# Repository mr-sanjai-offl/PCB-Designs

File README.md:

# PCB Designs

A collection of completed KiCad PCB design projects with automatically generated documentation and PCB renders.

## Projects

| Project Title | Description |
|---|---|
| [Queaky Stem Toy](./Queaky_STEM_Toy/README.md) | KiCad PCB design project. |

---

_Automatically updated: 2026-08-27 16:57 UTC_
_Total projects: 1_

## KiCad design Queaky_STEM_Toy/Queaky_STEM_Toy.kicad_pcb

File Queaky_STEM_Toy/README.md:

# Queaky Stem Toy

## Description
<!-- PROJECT_DESCRIPTION -->
KiCad PCB design project for Queaky Stem Toy.
<!-- /PROJECT_DESCRIPTION -->

## Board Specifications

| Specification | Details |
|---|---|
| Dimensions | 30.0 × 30.0 mm |
| Area | 900.0 mm² |
| Thickness | 1.6 mm |
| Copper Layers | 2 |

## Components (8)

| Reference | Value | Footprint | Description |
|---|---|---|---|
| C1 | 1nF | Capacitor_THT:C_Disc_D9.0mm_W5.0mm_P10.00mm | Unpolarized capacitor |
| C2 | 100uF | Capacitor_THT:CP_Radial_D8.0mm_P3.50mm | Polarized capacitor |
| R1 | 1K | Resistor_THT:R_Axial_DIN0309_L9.0mm_D3.2mm_P12.70mm_Horizontal | Resistor |
| R2 | 10K | Resistor_THT:R_Axial_DIN0309_L9.0mm_D3.2mm_P12.70mm_Horizontal | Resistor |
| TP1 | Battery | Connector_PinSocket_2.54mm:PinSocket_1x02_P2.54mm_Vertical | 2-polar test point |
| TP2 | Human_IP | Connector_PinSocket_2.54mm:PinSocket_1x02_P2.54mm_Vertical | 2-polar test point |
| TP3 | Buzzer | Connector_PinSocket_2.54mm:PinSocket_1x02_P2.54mm_Vertical | 2-polar test point |
| U1 | NE555P | Package_DIP:DIP-8_W7.62mm | Precision Timers, 555 compatible, PDIP-8 |

## PCB Renders

### Bottom View

### Rotating 3D View

### Top View

## KiCad Files

- `Queaky_STEM_Toy.kicad_pcb`
- `Queaky_STEM_Toy.kicad_prl`
- `Queaky_STEM_Toy.kicad_pro`
- `Queaky_STEM_Toy.kicad_sch`

---

_This README is automatically generated by GitHub Actions._

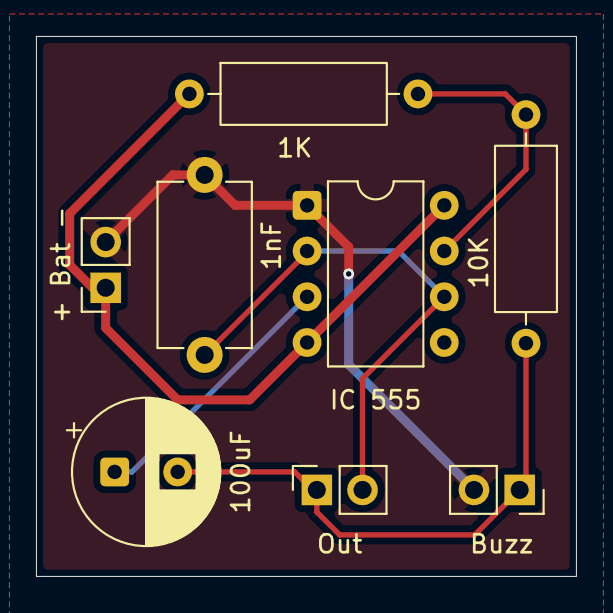
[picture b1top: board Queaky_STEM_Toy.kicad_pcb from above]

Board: 2 copper layers, 30.0 x 30.0 mm, 8 parts (0 on the bottom side), 6 nets.

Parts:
1K: 1K; R_Axial_DIN0309_L9.0mm_D3.2mm_P12.70mm_Horizontal
1nF: 1nF; C_Disc_D9.0mm_W5.0mm_P10.00mm
10K: 10K; R_Axial_DIN0309_L9.0mm_D3.2mm_P12.70mm_Horizontal
100uF: 100uF; CP_Radial_D8.0mm_P3.50mm
+ Bat -: Battery; PinSocket_1x02_P2.54mm_Vertical
Buzz: Buzzer; PinSocket_1x02_P2.54mm_Vertical
IC 555: NE555P; DIP-8_W7.62mm
Out: Human_IP; PinSocket_1x02_P2.54mm_Vertical

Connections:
/<NO NET>: 10K.2, 100uF.2, Buzz.1, Out.1
/DIS: 1K.2, 10K.1, IC 555.7 (DISCH)
/Out: 100uF.1, IC 555.3 (OUT)
/TR: 1nF.1, IC 555.2 (TRIG), IC 555.6 (THRES), Out.2
GND: 1nF.2, + Bat -.2, Buzz.2, IC 555.1 (GND)
VCC: 1K.1, + Bat -.1, IC 555.4 (~RST), IC 555.8 (VCC)

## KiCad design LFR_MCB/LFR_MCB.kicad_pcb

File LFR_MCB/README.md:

# Lfr Mcb

## Description
<!-- PROJECT_DESCRIPTION -->
KiCad PCB design project for Lfr Mcb.
<!-- /PROJECT_DESCRIPTION -->

## Board Specifications

| Specification | Details |
|---|---|
| Dimensions | 81.0 × 81.5 mm |
| Area | 6601.5 mm² |
| Thickness | 1.6 mm |
| Copper Layers | 2 |

## Components (17)

| Reference | Value | Footprint | Description |
|---|---|---|---|
| C1 | C | Capacitor_THT:C_Disc_D3.0mm_W1.6mm_P2.50mm | Unpolarized capacitor |
| C2 | C | Capacitor_THT:CP_Radial_D5.0mm_P2.50mm | Unpolarized capacitor |
| D1 | LED | LED_THT:LED_D5.0mm | Light emitting diode |
| D2 | D | Diode_THT:D_DO-41_SOD81_P10.16mm_Horizontal | Diode |
| J1 | Screw_Terminal_01x02 | TerminalBlock_Phoenix:TerminalBlock_Phoenix_MKDS-1,5-2-5.08_1x02_P5.08mm_Horizontal | Generic screw terminal, single row, 01x02, script generated (kicad-library-utils/schlib/autogen/connector/) |
| J10 | Conn_01x08_Socket | Connector_PinSocket_2.54mm:PinSocket_1x08_P2.54mm_Vertical | Generic connector, single row, 01x08, script generated |
| J2 | Screw_Terminal_01x02 | TerminalBlock_Phoenix:TerminalBlock_Phoenix_MKDS-1,5-2-5.08_1x02_P5.08mm_Horizontal | Generic screw terminal, single row, 01x02, script generated (kicad-library-utils/schlib/autogen/connector/) |
| J3 | Screw_Terminal_01x02 | TerminalBlock_Phoenix:TerminalBlock_Phoenix_MKDS-1,5-2-5.08_1x02_P5.08mm_Horizontal | Generic screw terminal, single row, 01x02, script generated (kicad-library-utils/schlib/autogen/connector/) |
| J4 | Conn_01x15_Socket | Connector_PinSocket_2.54mm:PinSocket_1x15_P2.54mm_Vertical | Generic connector, single row, 01x15, script generated |
| J5 | Conn_01x15_Socket | Connector_PinSocket_2.54mm:PinSocket_1x15_P2.54mm_Vertical | Generic connector, single row, 01x15, script generated |
| J6 | Conn_01x15_Socket | Connector_PinSocket_2.54mm:PinSocket_1x15_P2.54mm_Vertical | Generic connector, single row, 01x15, script generated |
| J9 | Conn_01x08_Socket | Connector_PinSocket_2.54mm:PinSocket_1x08_P2.54mm_Vertical | Generic connector, single row, 01x08, script generated |
| R1 | 360 | Resistor_THT:R_Axial_DIN0204_L3.6mm_D1.6mm_P5.08mm_Horizontal | Resistor |
| SW1 | SW_Wuerth_450301014042 | Button_Switch_THT:SW_Slide-03_Wuerth-WS-SLTV_10x2.5x6.4_P2.54mm | Switch slide, single pole double throw |
| SW2 | SW_Push | Button_Switch_THT:SW_CW_GPTS203211B | Push button switch, generic, two pins |
| SW3 | SW_Push | Button_Switch_THT:SW_CW_GPTS203211B | Push button switch, generic, two pins |
| U1 | LM2931AZ-5.0_TO92 | Package_TO_SOT_THT:TO-92_Inline | 100mA Low drop-out regulator, Fixed Output 5V, TO-92 |

## PCB Renders

### Bottom View

### Rotating 3D View

### Top View

## KiCad Files

- `LFR_MCB.kicad_pcb`
- `LFR_MCB.kicad_prl`
- `LFR_MCB.kicad_pro`
- `LFR_MCB.kicad_sch`

---

_This README is automatically generated by GitHub Actions._

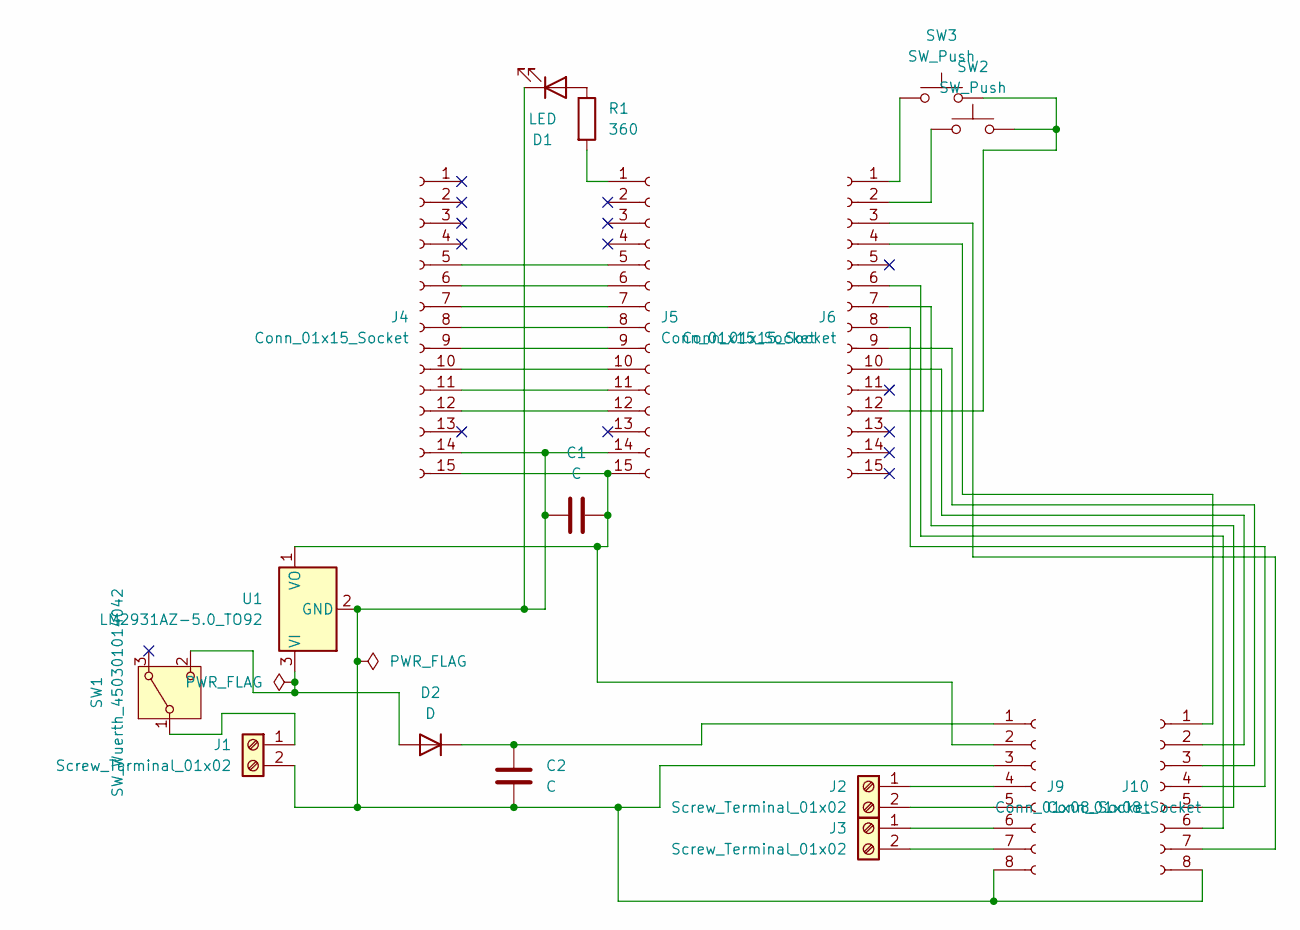
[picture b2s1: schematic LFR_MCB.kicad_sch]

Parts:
C1: C; C_Disc_D3.0mm_W1.6mm_P2.50mm
C2: C; CP_Radial_D5.0mm_P2.50mm
D1: LED; LED_D5.0mm
D2: D; D_DO-41_SOD81_P10.16mm_Horizontal
J1, J2, J3: Screw_Terminal_01x02; TerminalBlock_Phoenix_MKDS-1,5-2-5.08_1x02_P5.08mm_Horizont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
J4, J5, J6: Conn_01x15_Socket; PinSocket_1x15_P2.54mm_Vertical
J9, J10: Conn_01x08_Socket; PinSocket_1x08_P2.54mm_Vertical
R1: 360; R_Axial_DIN0204_L3.6mm_D1.6mm_P5.08mm_Horizontal
SW1: SW_Wuerth_450301014042; SW_Slide-03_Wuerth-WS-SLTV_10x2.5x6.4_P2.54mm
SW2, SW3: SW_Push; SW_CW_GPTS203211B
U1: LM2931AZ-5.0_TO92; TO-92_Inline

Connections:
unnamed: D1.2 (A), R1.1
unnamed: C1.1, C2.2, D1.1 (K), J1.2, J4.14, J5.14, J9.3, J9.8, J10.8, U1.2 (GND)
unnamed: D2.2 (A), SW1.2 (C), U1.3 (VI)
unnamed: C2.1, D2.1 (K), J9.1
unnamed: J1.1, SW1.1 (B)
unnamed: J2.1, J9.4
unnamed: J2.2, J9.5
unnamed: J3.1, J9.6
unnamed: J3.2, J9.7
unnamed: J4.5, J5.5
unnamed: J4.6, J5.6
unnamed: J4.7, J5.7
unnamed: J4.8, J5.8
unnamed: J4.9, J5.9
unnamed: J4.10, J5.10
unnamed: J4.11, J5.11
unnamed: J4.12, J5.12
unnamed: C1.2, J4.15, J5.15, J9.2, U1.1 (VO)
unnamed: J5.1, R1.2
unnamed: J6.1, SW3.1
unnamed: J6.2, SW2.1
unnamed: J6.12, SW2.2, SW3.2
unnamed: J6.4, J10.1
unnamed: J6.10, J10.2
unnamed: J6.9, J10.3
unnamed: J6.8, J10.4
unnamed: J6.7, J10.5
unnamed: J6.6, J10.6
unnamed: J6.3, J10.7

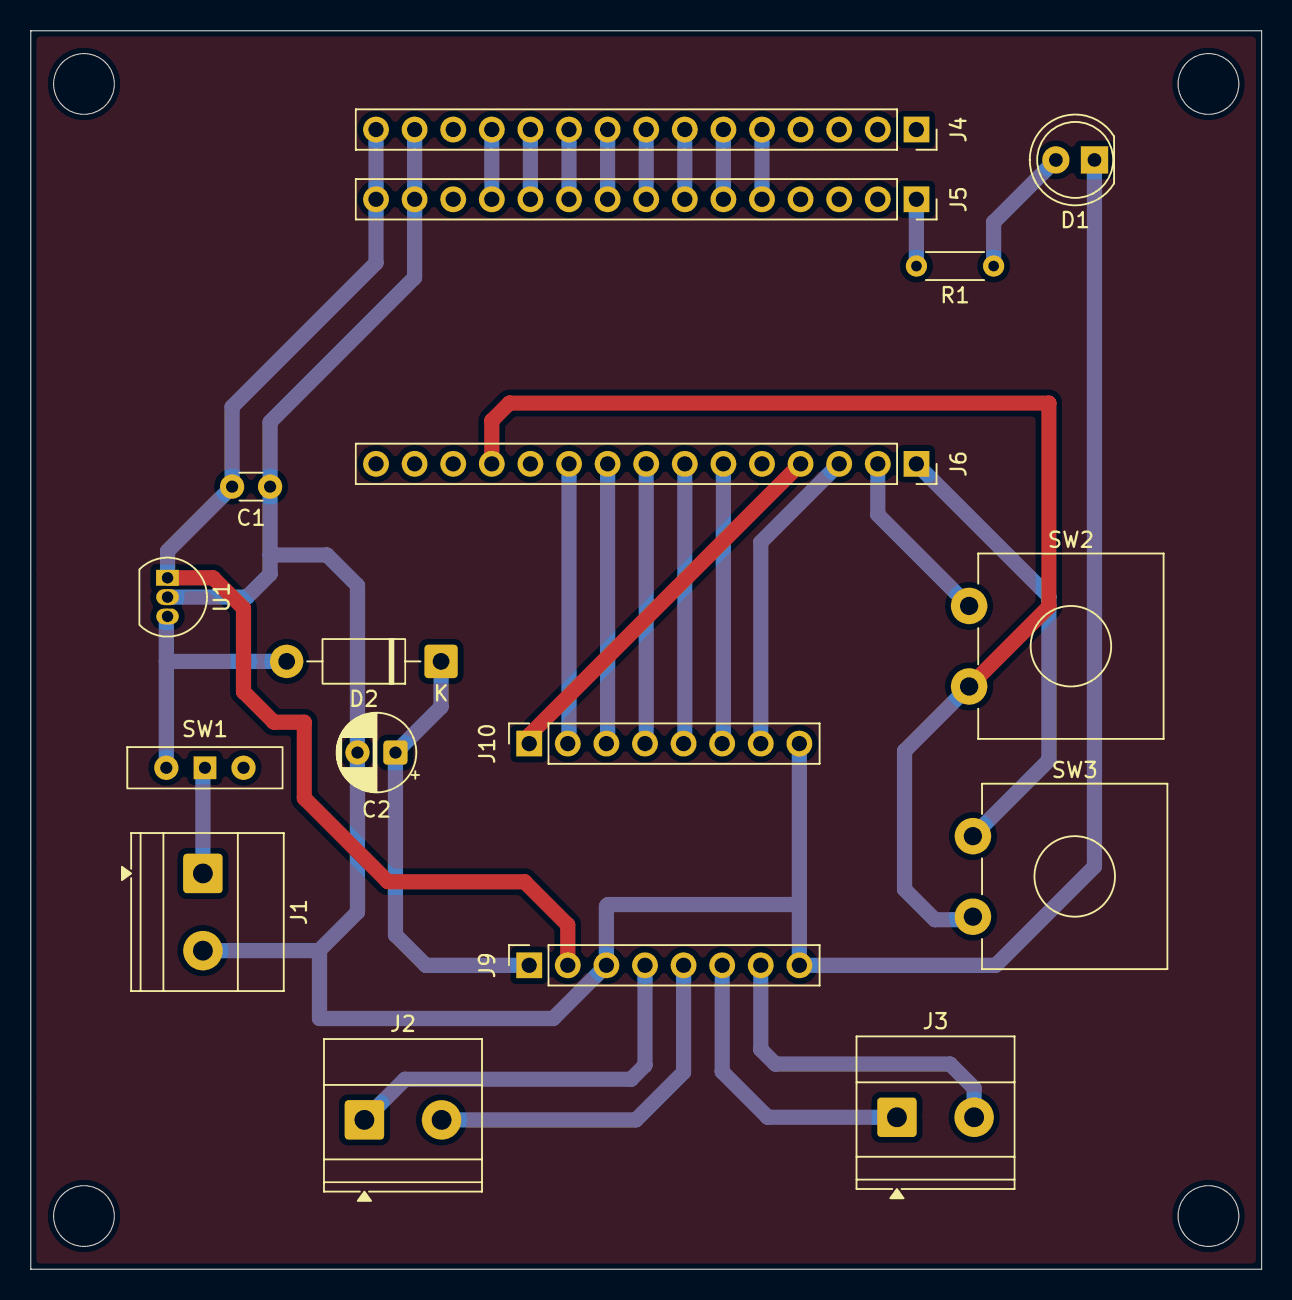
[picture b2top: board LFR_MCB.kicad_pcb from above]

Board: 2 copper layers, 81.0 x 81.5 mm, 17 parts (0 on the bottom side), 29 nets.

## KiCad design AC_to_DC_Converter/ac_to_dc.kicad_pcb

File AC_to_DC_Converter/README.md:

# Ac To Dc Converter

## Description
<!-- PROJECT_DESCRIPTION -->
KiCad PCB design project for Ac To Dc Converter.
<!-- /PROJECT_DESCRIPTION -->

## Board Specifications

| Specification | Details |
|---|---|
| Dimensions | 48.0 × 34.5 mm |
| Area | 1656.0 mm² |
| Thickness | 1.6 mm |
| Copper Layers | 2 |

## Components (10)

| Reference | Value | Footprint | Description |
|---|---|---|---|
| C1 | C_Polarized | Capacitor_THT:CP_Radial_D8.0mm_P5.00mm | Polarized capacitor |
| D1 | D | Diode_THT:D_A-405_P10.16mm_Horizontal | Diode |
| D2 | D | Diode_THT:D_A-405_P10.16mm_Horizontal | Diode |
| D3 | D | Diode_THT:D_A-405_P10.16mm_Horizontal | Diode |
| D4 | D | Diode_THT:D_A-405_P10.16mm_Horizontal | Diode |
| D5 | LED | LED_THT:LED_D5.0mm | Light emitting diode |
| J1 | Screw_Terminal_01x02 | TerminalBlock_Phoenix:TerminalBlock_Phoenix_MKDS-1,5-2-5.08_1x02_P5.08mm_Horizontal | Generic screw terminal, single row, 01x02, script generated (kicad-library-utils/schlib/autogen/connector/) |
| J2 | Screw_Terminal_01x02 | TerminalBlock_Phoenix:TerminalBlock_Phoenix_MKDS-1,5-2-5.08_1x02_P5.08mm_Horizontal | Generic screw terminal, single row, 01x02, script generated (kicad-library-utils/schlib/autogen/connector/) |
| R1 | R | Resistor_THT:R_Axial_DIN0204_L3.6mm_D1.6mm_P5.08mm_Vertical | Resistor |
| R2 | R | Resistor_THT:R_Axial_DIN0204_L3.6mm_D1.6mm_P5.08mm_Vertical | Resistor |

## PCB Renders

### Bottom View

### Rotating 3D View

### Top View

## KiCad Files

- `ac_to_dc.kicad_pcb`
- `ac_to_dc.kicad_pro`
- `ac_to_dc.kicad_sch`

---

_This README is automatically generated by GitHub Actions._

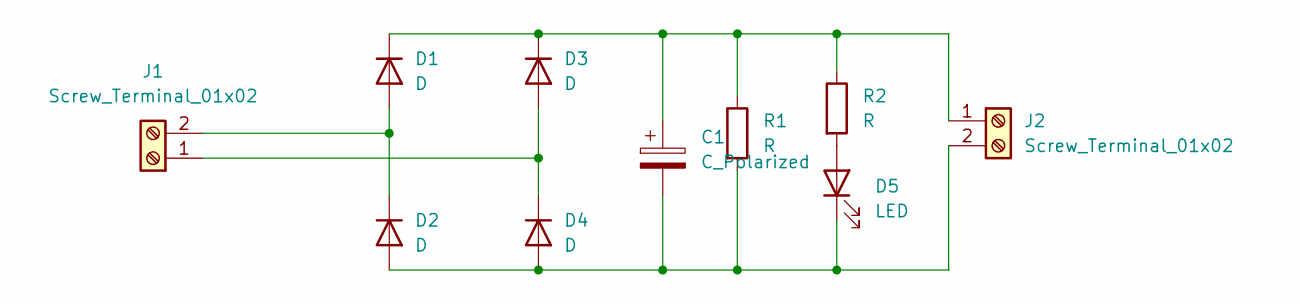
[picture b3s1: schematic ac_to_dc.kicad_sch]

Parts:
C1: C_Polarized; CP_Radial_D8.0mm_P5.00mm
D1, D2, D3, D4: D; D_A-405_P10.16mm_Horizontal
D5: LED; LED_D5.0mm
J1, J2: Screw_Terminal_01x02; TerminalBlock_Phoenix_MKDS-1,5-2-5.08_1x02_P5.08mm_Horizont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
R1, R2: R; R_Axial_DIN0204_L3.6mm_D1.6mm_P5.08mm_Vertical

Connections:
unnamed: D1.2 (A), D2.1 (K), J1.2
unnamed: C1.1, D1.1 (K), D3.1 (K), J2.1, R1.1, R2.1
unnamed: C1.2, D2.2 (A), D4.2 (A), D5.1 (K), J2.2, R1.2
unnamed: D3.2 (A), D4.1 (K), J1.1
unnamed: D5.2 (A), R2.2

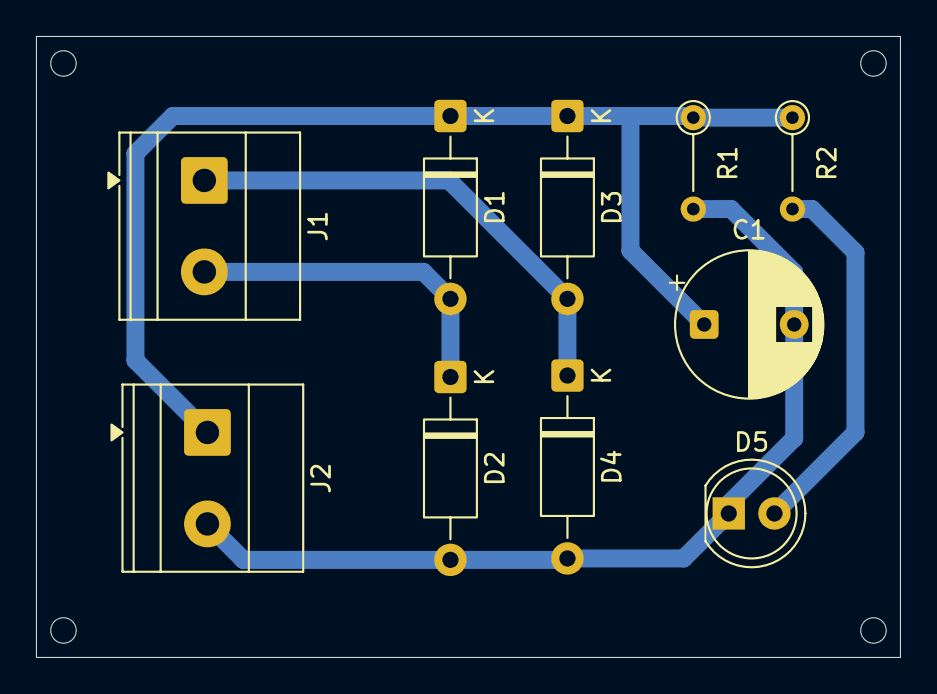
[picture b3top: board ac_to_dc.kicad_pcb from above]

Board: 2 copper layers, 48.0 x 34.5 mm, 10 parts (0 on the bottom side), 5 nets.
